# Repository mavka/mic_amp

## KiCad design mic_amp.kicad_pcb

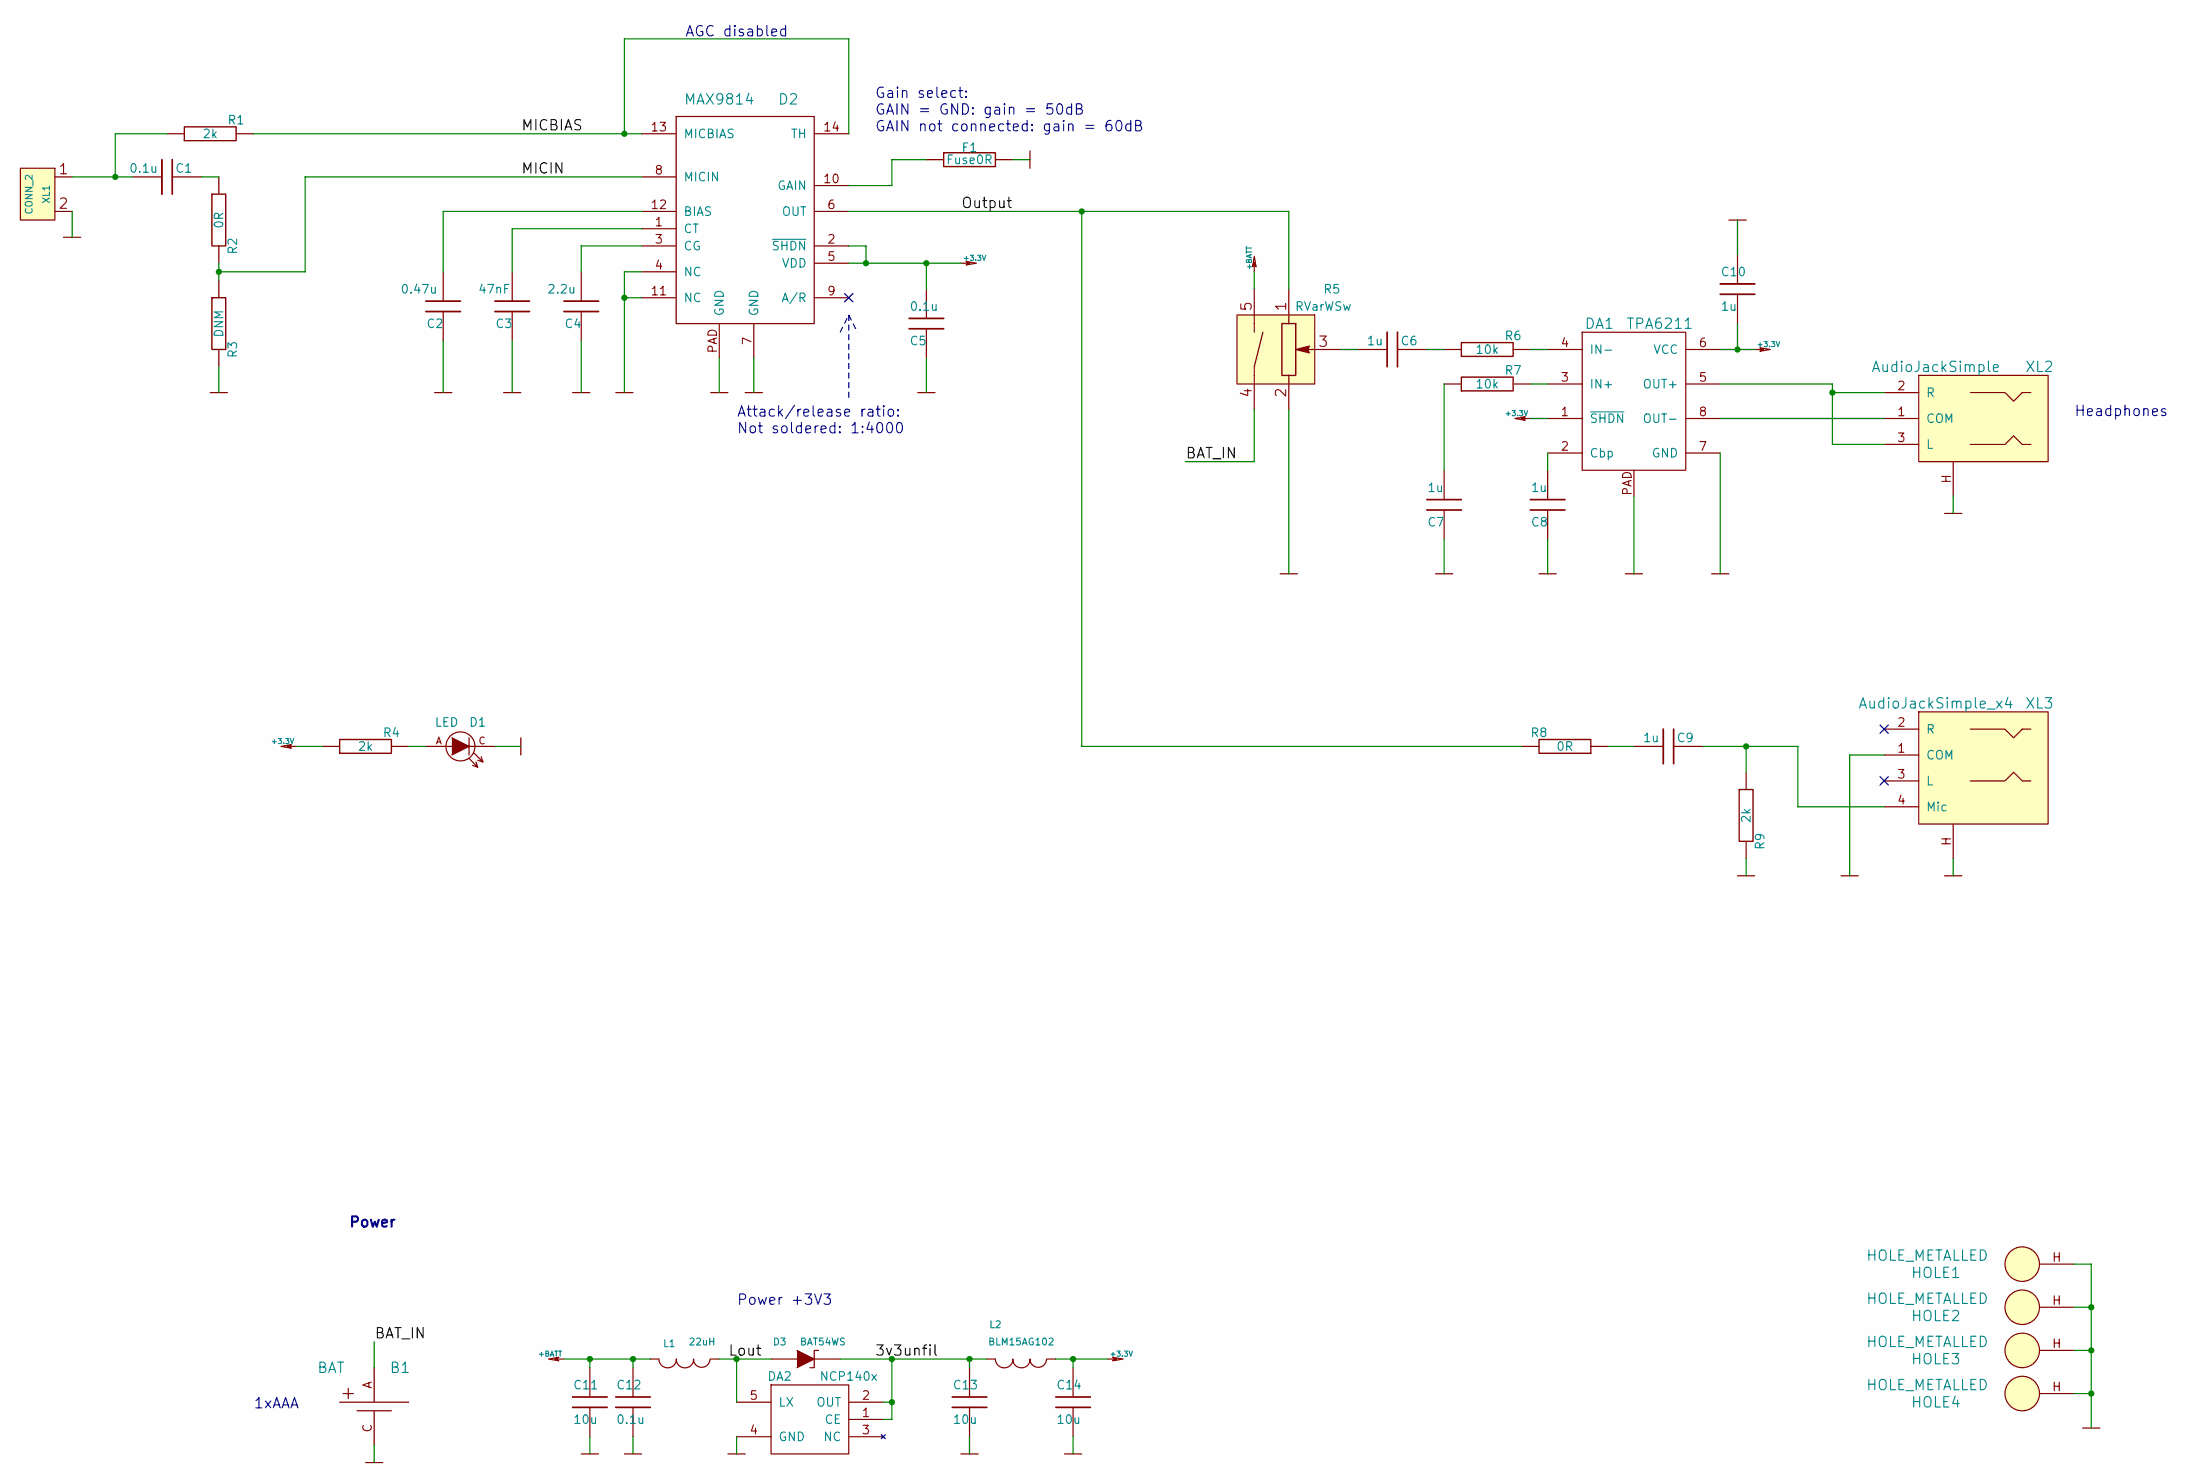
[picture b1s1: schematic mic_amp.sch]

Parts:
B1: BAT; BATTERY_AAA_X1
C1, C5, C12: 0.1u; CAP_0603
C2: 0.47u; CAP_0603
C3: 47nF; CAP_0603
C4: 2.2u; CAP_0603
C6, C7, C8, C9, C10: 1u; CAP_0603
C11, C13, C14: 10u; CAP_0603
D1: LED; LED_Through-Hole-3mm
D2: MAX9814; DFN14
D3: BAT54WS; SOD323
DA1: TPA6211; DRB8
DA2: NCP140x; SOT23-5
F1: Fuse0R; RES_0603_SOLDERFUSE
HOLE1, HOLE2, HOLE3, HOLE4: HOLE_METALLED; Hole3d3_out5d5mm
L1: 22uH; IND_1210_LQH32C
L2: BLM15AG102; IND_0402
R1, R4, R9: 2k; RES_0603
R2, R8: 0R; RES_0603
R3: DNM; RES_0603
R5: RVarWSw; RVar_SP3_R
R6, R7: 10k; RES_0603
XL1: CONN_2; PLS-2
XL2: AudioJackSimple; AUDIO_CKX3_5_30
XL3: AudioJackSimple_x4; Audio_ST013

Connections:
+3.3V: C5.1, C10.1, C14.2, D2.2 (~SHDN), D2.5 (VDD), DA1.1 (~SHDN), DA1.6 (VCC), L2.1, R4.1
+BATT: C11.2, C12.2, L1.2, R5.5
/3v3unfil: C13.2, D3.C, DA2.1 (CE), DA2.2 (OUT), L2.2
/BAT_IN: B1.A, R5.4
/Lout: D3.A, DA2.5 (LX), L1.1
/MICBIAS: D2.13 (MICBIAS), D2.14 (TH), R1.2
/MICIN: D2.8 (MICIN), R2.2, R3.1
/Output: D2.6 (OUT), R5.1, R8.2
GND: B1.C, C2.2, C3.2, C4.2, C5.2, C7.2, C8.2, C10.2, C11.1, C12.1, C13.1, C14.1, D1.C, D2.4 (NC), D2.7 (GND), D2.11 (NC), D2.PAD (GND), DA1.7 (GND), DA1.PAD, DA2.4 (GND), F1.2, HOLE1.H, HOLE2.H, HOLE3.H, HOLE4.H, R3.2, R5.2, R9.2, XL1.2 (PM), XL2.H, XL3.1 (COM), XL3.H
unnamed: C1.1, R1.1, XL1.1
unnamed: C1.2, R2.1
unnamed: C2.1, D2.12 (BIAS)
unnamed: C3.1, D2.1 (CT)
unnamed: C4.1, D2.3 (CG)
unnamed: C6.1, R5.3
unnamed: C6.2, R6.1
unnamed: C7.1, R7.1
unnamed: C8.1, DA1.2 (Cbp)
unnamed: C9.1, R8.1
unnamed: C9.2, R9.1, XL3.4 (Mic)
unnamed: D1.A, R4.2
unnamed: D2.10 (GAIN), F1.1
unnamed: DA1.3 (IN+), R7.2
unnamed: DA1.4 (IN-), R6.2
unnamed: DA1.5 (OUT+), XL2.2 (R), XL2.3 (L)
unnamed: DA1.8 (OUT-), XL2.1 (COM)

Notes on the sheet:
Attack/release ratio: Not soldered: 1:4000
Gain select: GAIN = GND: gain = 50dB GAIN not connected: gain = 60dB
AGC disabled
Power
1xAAA
Headphones
Power +3V3

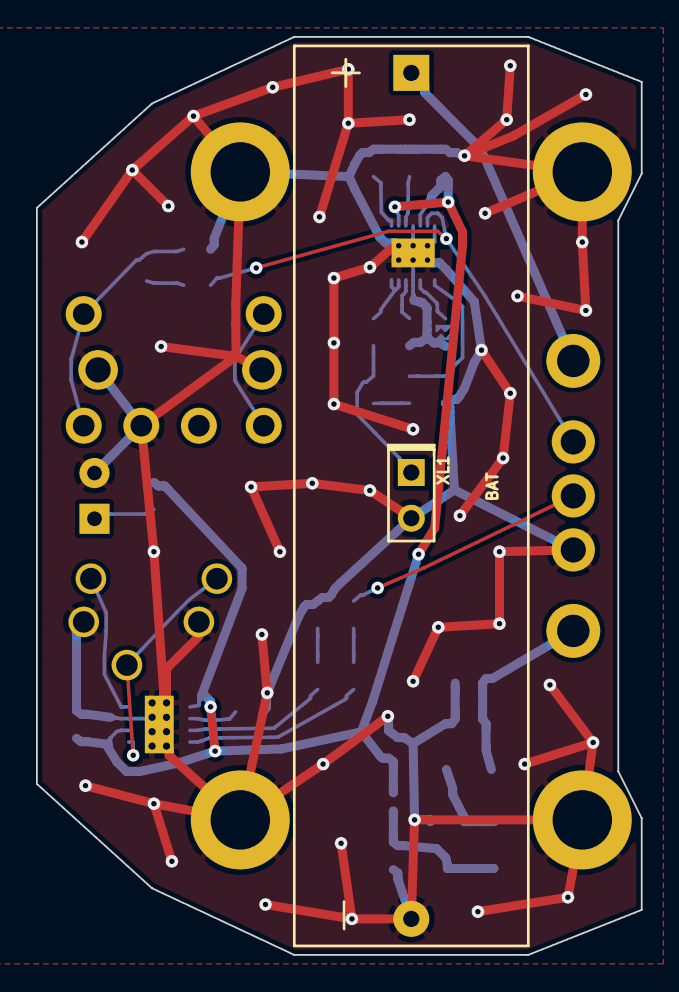
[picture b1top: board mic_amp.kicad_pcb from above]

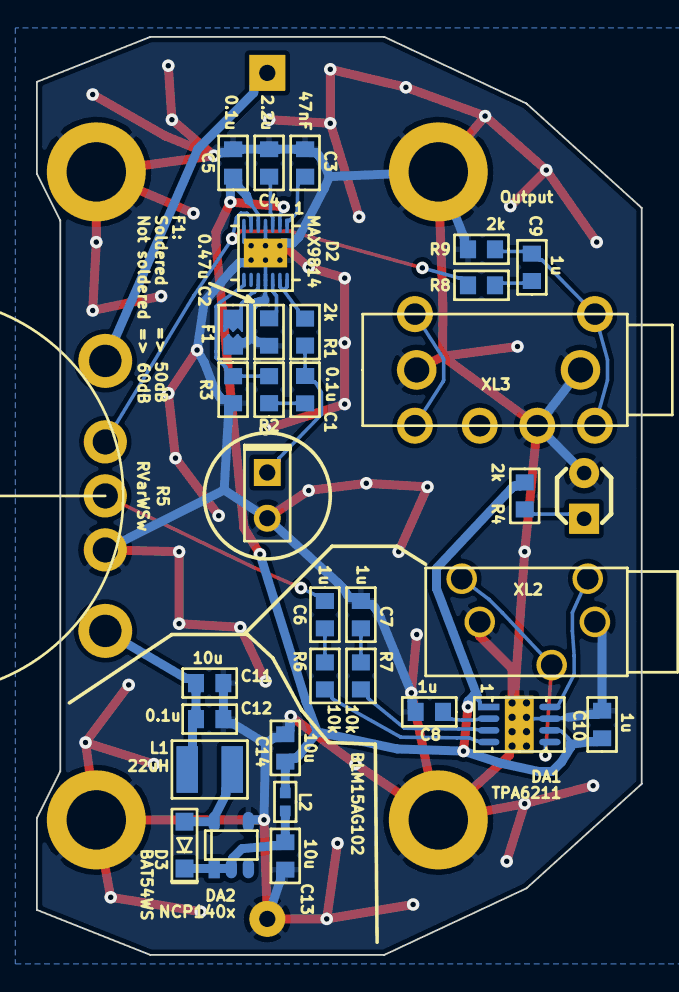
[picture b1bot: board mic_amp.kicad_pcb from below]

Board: 2 copper layers, 33.6 x 51.0 mm, 39 parts (33 on the bottom side), 26 nets.

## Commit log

2015-10-09 :circus_tent: Added .gitattributes & .gitignore files
2015-10-09 scheme add
2015-10-15 * Sch edited and checked
2015-10-18 * Sch done + Components association
2015-10-18 pcb add
2015-10-18 filling wanted :)
2015-10-19 plot and drl
2015-11-08 порядок наводим
2015-11-08 just pics :)
2016-06-25 With 3v battery
2016-07-06 2xAAA sch
2016-07-07 + Pcb sent to manufacturing
2016-08-29 Proceeding with sch
2016-09-01 + mic amp 2.1 pcb ready
2016-09-08 * Move pcb to PCB + Steto fw
2016-09-09 + Btns + Adc + on/off btn
2016-09-10 DigPot works
2016-09-10 + Non-linear volume adjustment RC
2016-09-11 + Smooth LED + Sequences + Discharged indication RC2
2016-09-12 * Btns exchanged * Delay before repeat shortened RC
